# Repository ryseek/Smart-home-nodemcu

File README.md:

# ESP8266 WiFi light controller
## Progress
- [x] Electric scheme
- [x] PCB design
- [ ] PCB prototype
- [ ] Firmware

## Electric scheme

## PCB Design

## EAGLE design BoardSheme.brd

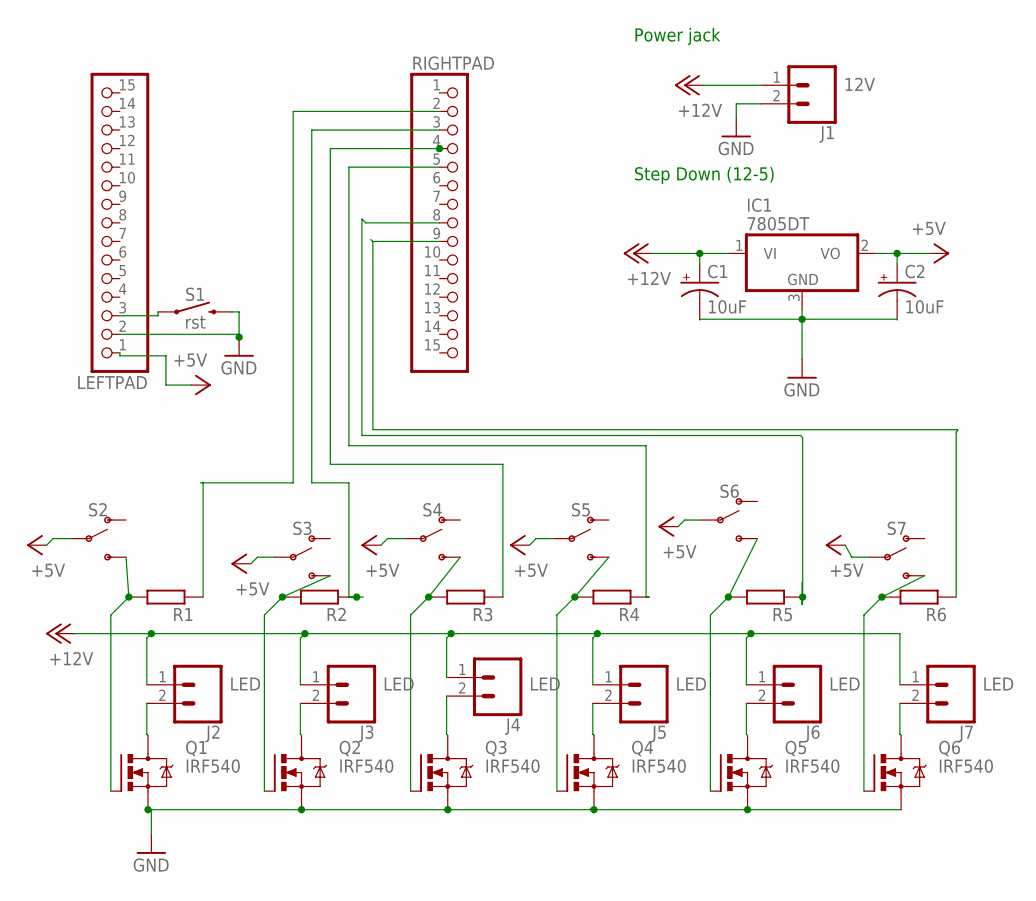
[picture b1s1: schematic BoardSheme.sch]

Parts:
C1, C2: 10uF; CPOL-RADIAL-2.5MM-5MM
IC1: 7805DT; TO252
J1: CONN_02PTH4; 1X02_XTRA_BIG; VOLTAGE 12V
J2, J3, J4, J5, J6, J7: CONN_02PTH4; 1X02_XTRA_BIG; VOLTAGE LED
LEFTPAD: PINHD-1X15; 1X15
Q1, Q2, Q3, Q4, Q5, Q6: IRF540; TO220BV
R1, R2, R3, R4, R5, R6: RR1206; R1206
RIGHTPAD: PINHD-1X15; 1X15
S1: rst; TACTILE_SWITCH_PTH_6.0MM_KIT
S2, S3, S4, S5, S6, S7: SWITCH-SPDT-PTH-11.6X4.0MM; SWITCH_SPDT_PTH_11.6X4.0MM

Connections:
+5V: C2.1 (+), IC1.2 (VO), LEFTPAD.1, S2.2, S3.2, S4.2, S5.2, S6.2, S7.2
+12V: C1.1 (+), IC1.1 (VI), J1.1, J2.1, J3.1, J4.1, J5.1, J6.1, J7.1
GND: C1.2 (-), C2.2 (-), IC1.3 (GND), J1.2, LEFTPAD.2, Q1.S, Q2.S, Q3.S, Q4.S, Q5.S, Q6.S, S1.3 (2)
unnamed: LEFTPAD.3, S1.1
unnamed: Q1.G, R1.2, S2.3 (S)
unnamed: J2.2, Q1.D
unnamed: J3.2, Q2.D
unnamed: J4.2, Q3.D
unnamed: J5.2, Q4.D
unnamed: J6.2, Q5.D
unnamed: J7.2, Q6.D
unnamed: Q2.G, R2.2, S3.3 (S)
unnamed: Q3.G, R3.2, S4.3 (S)
unnamed: Q4.G, R4.2, S5.3 (S)
unnamed: Q5.G, R5.2, S6.3 (S)
unnamed: Q6.G, R6.2, S7.3 (S)
unnamed: R3.1, RIGHTPAD.4
unnamed: R2.1, RIGHTPAD.3
unnamed: R1.1, RIGHTPAD.2
unnamed: R4.1, RIGHTPAD.5
unnamed: R5.1, RIGHTPAD.8
unnamed: R6.1, RIGHTPAD.9

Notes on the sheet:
Step Down (12-5)
Power jack

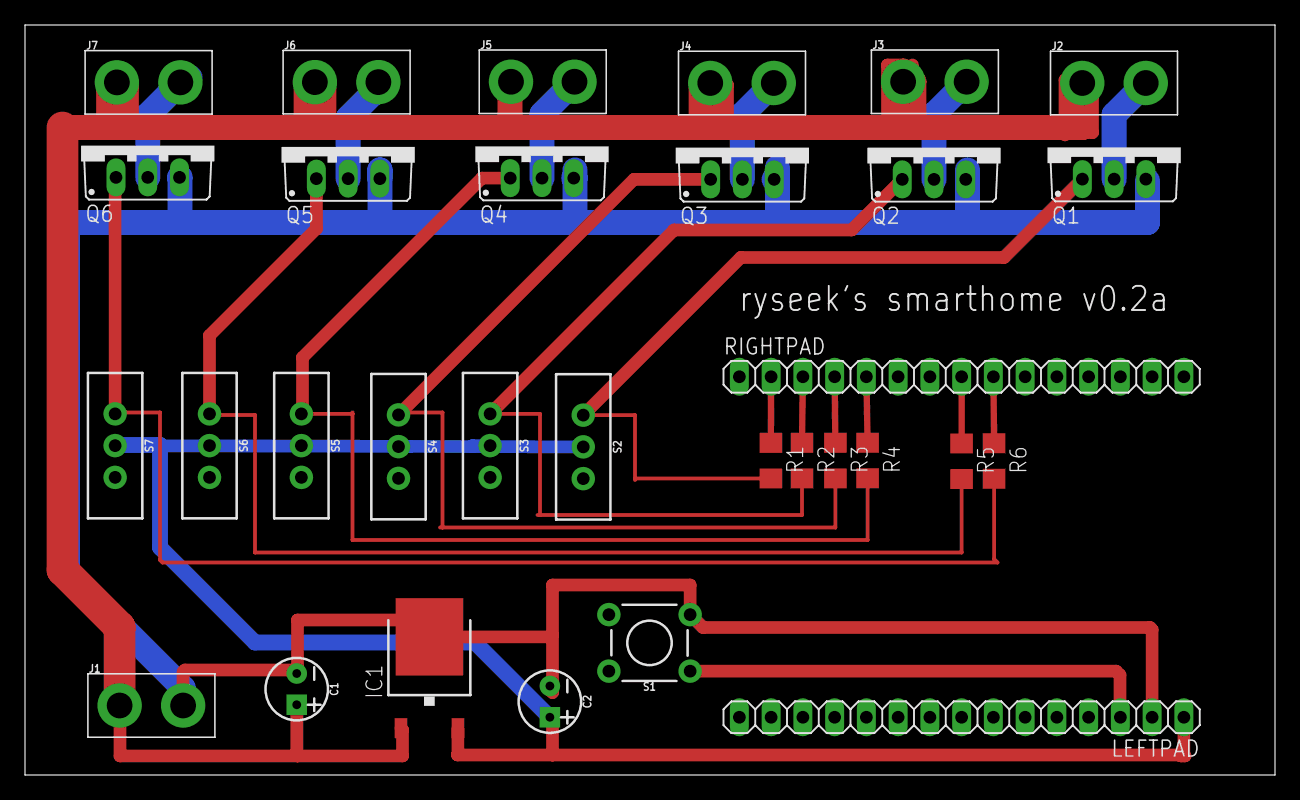
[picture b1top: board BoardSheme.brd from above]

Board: 2 copper layers, 100.0 x 60.0 mm, 31 parts (0 on the bottom side), 22 nets.

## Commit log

2018-01-18 V0.1 completed
2018-01-18 Readme update
2018-01-20 small update to pcb
    Made connections with power lines stronger

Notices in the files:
parts and their libraries:
SparkFun-Capacitors: Licensing: Creative Commons ShareAlike 4.0 International - https://creativecommons.org/licenses/by-sa/4.0
